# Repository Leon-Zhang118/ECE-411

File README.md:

# ECE Capstone Project 

# Teammates:

  Zheliang Zhang 

  Jinghan Zhang 

  Danny Wu

  Benjamin Vu

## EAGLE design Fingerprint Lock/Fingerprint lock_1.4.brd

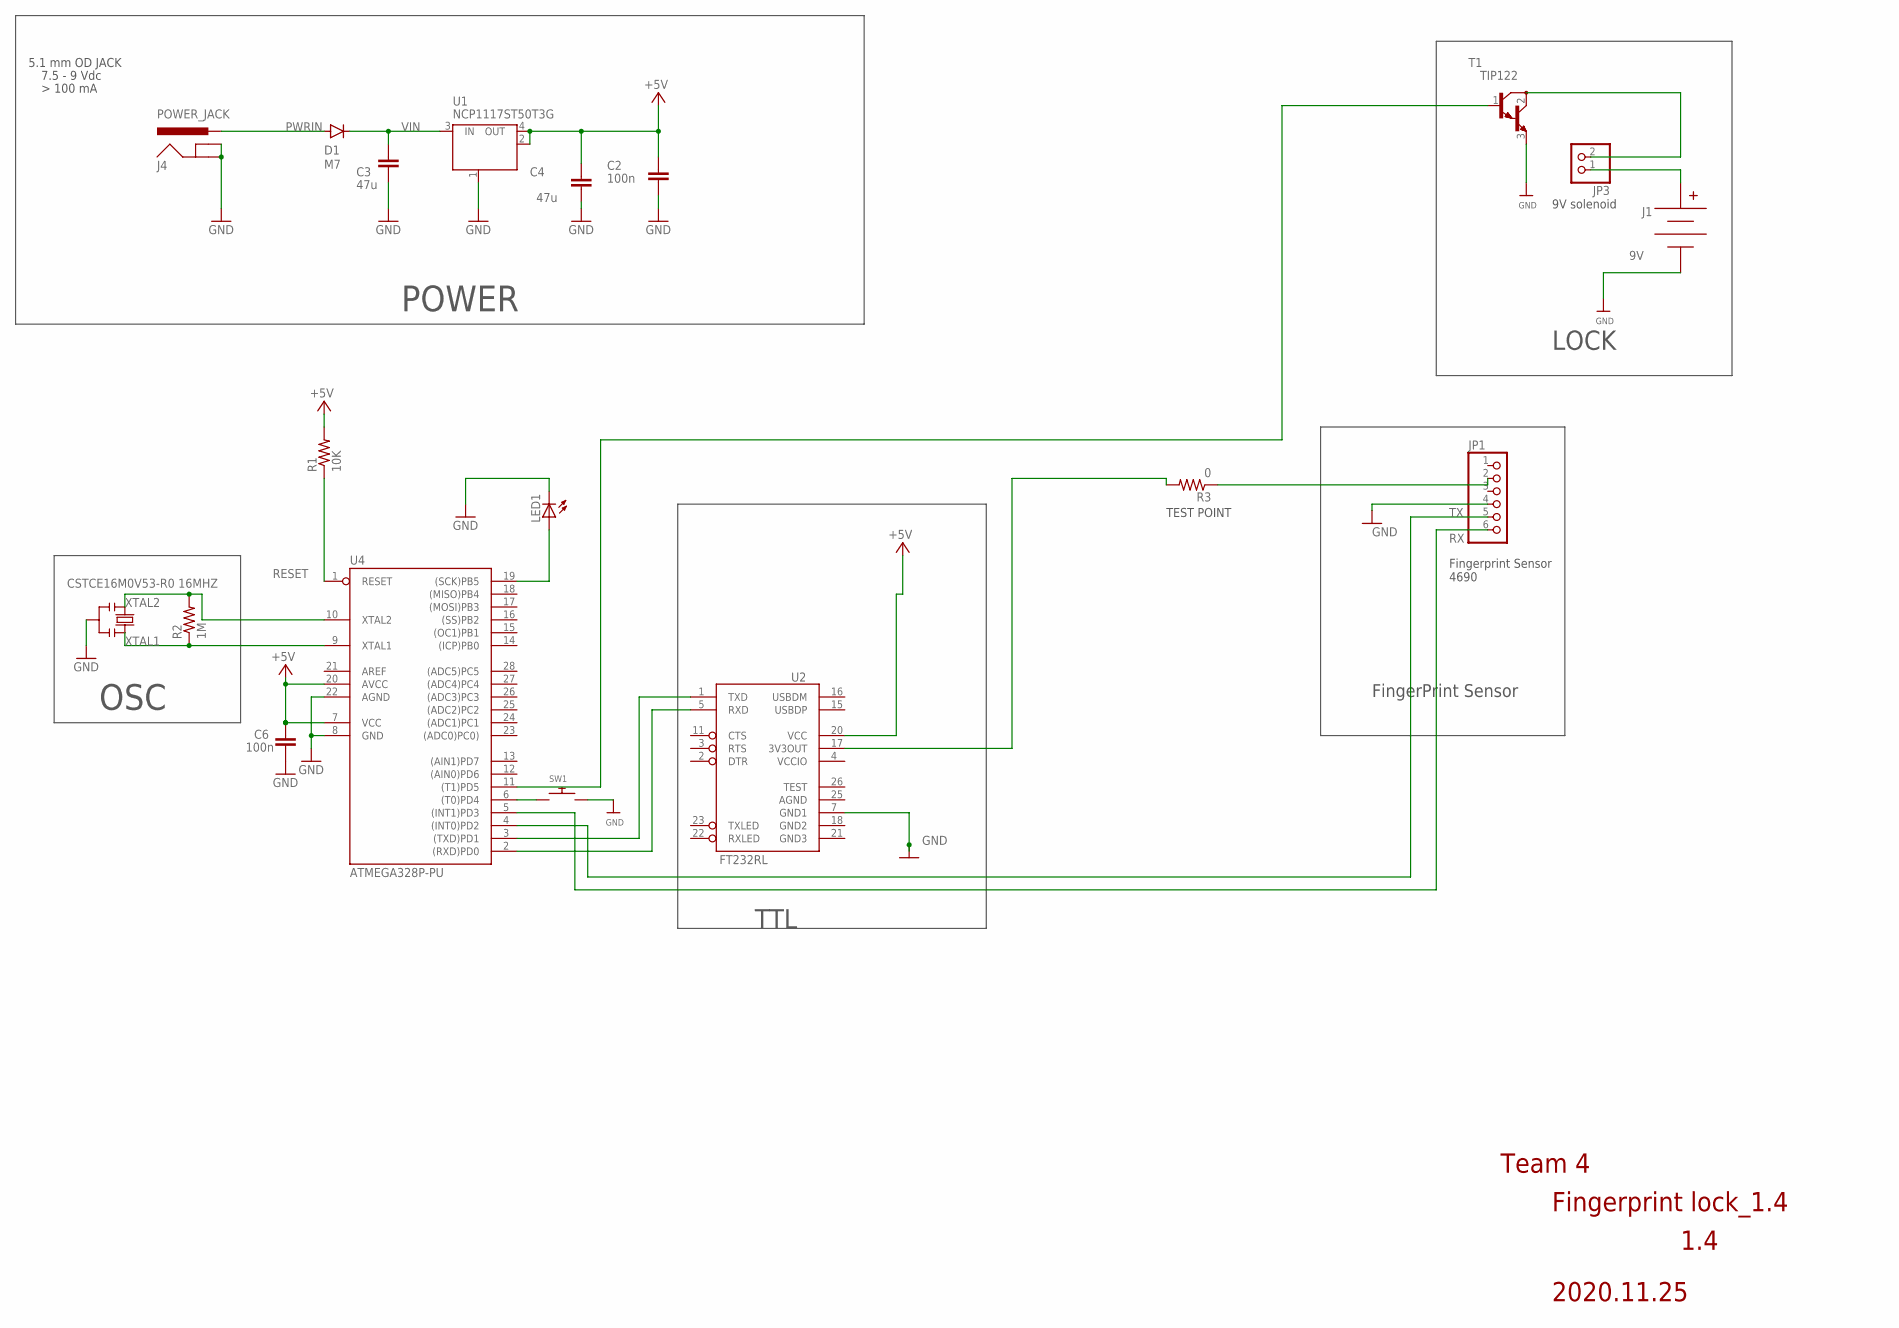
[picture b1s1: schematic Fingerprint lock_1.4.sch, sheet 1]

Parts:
C2, C6: 100n; C0805
C3, C4: 47u; C0805
D1: M7; SMB
J1: 9V; BC9VPC
J4: POWER_JACK; POWER_JACK_PTH
JP1: PINHD-1X6B; 1X06-BIG
JP3: PINHD-1X2; 1X02
LED1: LEDB155; Q62902-B155
R1: 10K; R0805
R2: 1M; R0805
R3: 0; R0805
SW1: SWITCH_PUSHBUTTONEVQ-PE; TACT_PANA-EVQ
T1: TIP122; TO220
U1: NCP1117ST50T3G; SOT223
U2: FT232RL; SSOP28DB
U4: ATMEGA328P-PU; DIL28-3
X1: CSTCE16M0V53-R0 16MHZ; RESONATOR

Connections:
9V: J1.V+, JP3.1
+5V: C2.2, C4.2, C6.2, R1.2, U1.2 (OUT), U1.4 (OUT), U2.20 (VCC), U4.7 (VCC), U4.20 (AVCC)
AGND: U2.25 (AGND)
GND: C2.1, C3.1, C4.1, C6.1, J1.V-, J4.GND, J4.GNDBREAK, JP1.4, LED1.K (C), SW1.P$2, T1.3 (E), U1.1 (GND/ADJ), U2.7 (GND1), U4.8 (GND), U4.22 (AGND), X1.2
GND2: U2.18 (GND2)
GND3: U2.21 (GND3)
LED: LED1.A, U4.19 ((SCK)PB5)
LOCK: T1.1 (B), U4.11 ((T1)PD5)
unnamed: JP1.6, U4.5 ((INT1)PD3)
unnamed: JP1.2, R3.1
unnamed: U2.5 (RXD), U4.2 ((RXD)PD0)
unnamed: U2.1 (TXD), U4.3 ((TXD)PD1)
unnamed: R3.2, U2.17 (3V3OUT)
unnamed: JP3.2, T1.2 (C)
unnamed: SW1.P$1, U4.6 ((T0)PD4)
PWRIN: D1.A, J4.PWR
RESET: R1.1, U4.1 (RESET)
TXD: JP1.5, U4.4 ((INT0)PD2)
VCCIO: U2.4 (VCCIO)
VIN: C3.2, D1.C, U1.3 (IN)
XTAL1: R2.1, U4.9 (XTAL1), X1.3
XTAL2: R2.2, U4.10 (XTAL2), X1.1

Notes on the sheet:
7.5 - 9 Vdc
POWER
OSC
5.1 mm OD JACK
Team 4
Fingerprint Sensor 4690
LOCK
FingerPrint Sensor
2020.11.25
TTL
9V solenoid
TEST POINT
Fingerprint lock_1.4
1.4

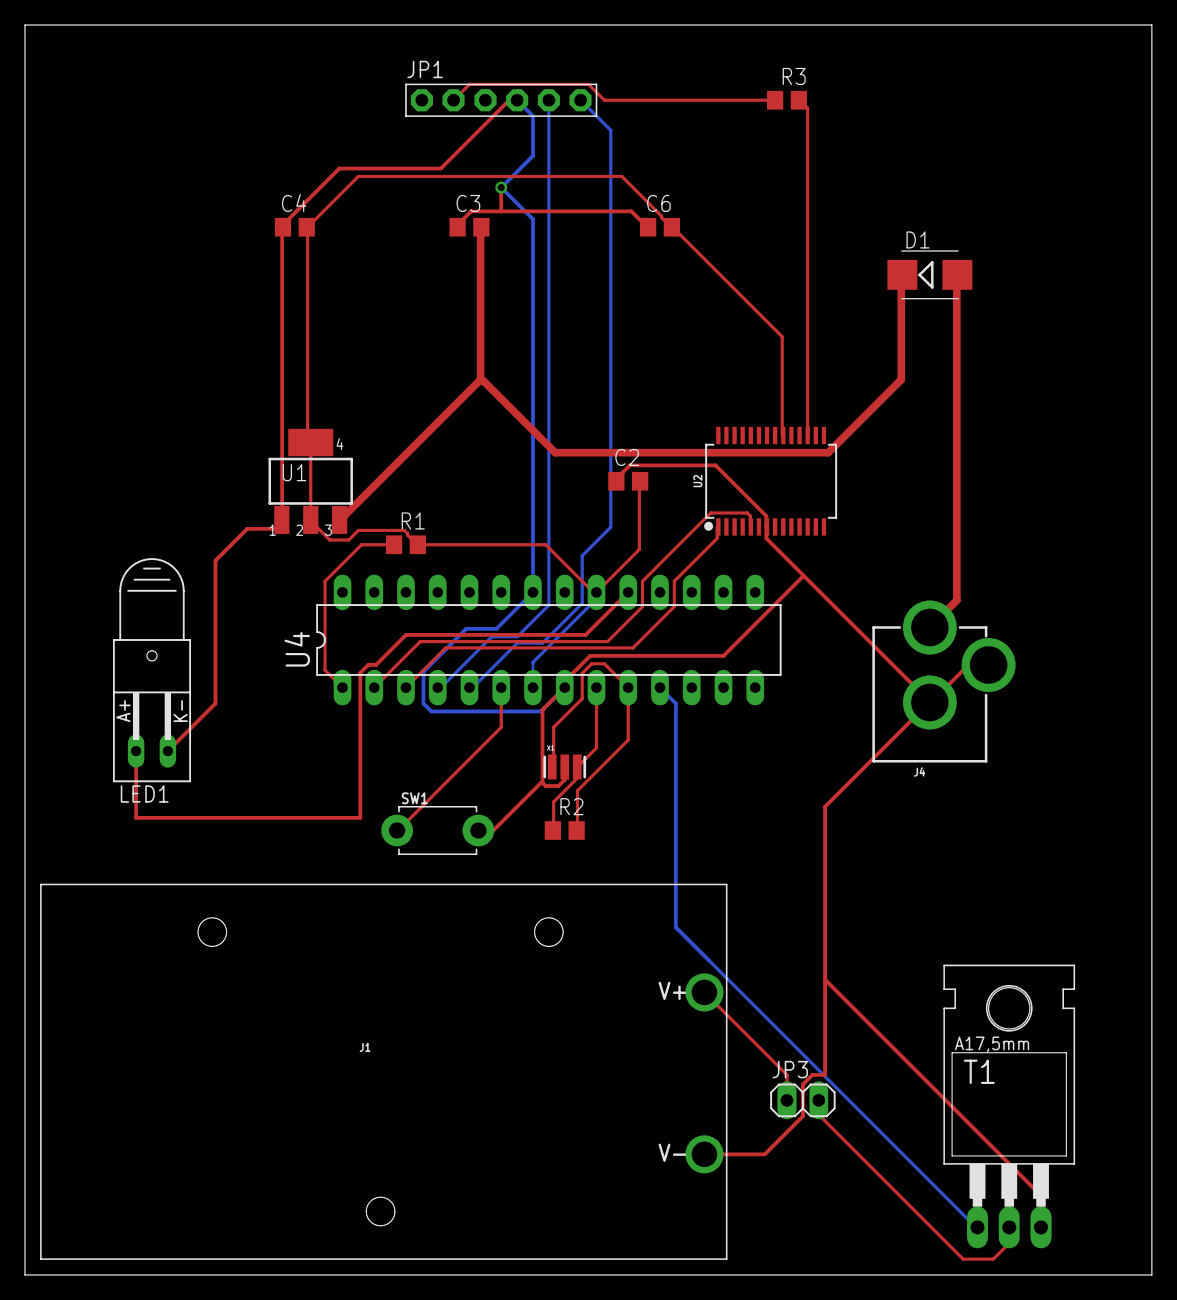
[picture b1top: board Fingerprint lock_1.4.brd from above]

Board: 4 copper layers, 90.2 x 100.0 mm, 19 parts (0 on the bottom side), 18 nets.

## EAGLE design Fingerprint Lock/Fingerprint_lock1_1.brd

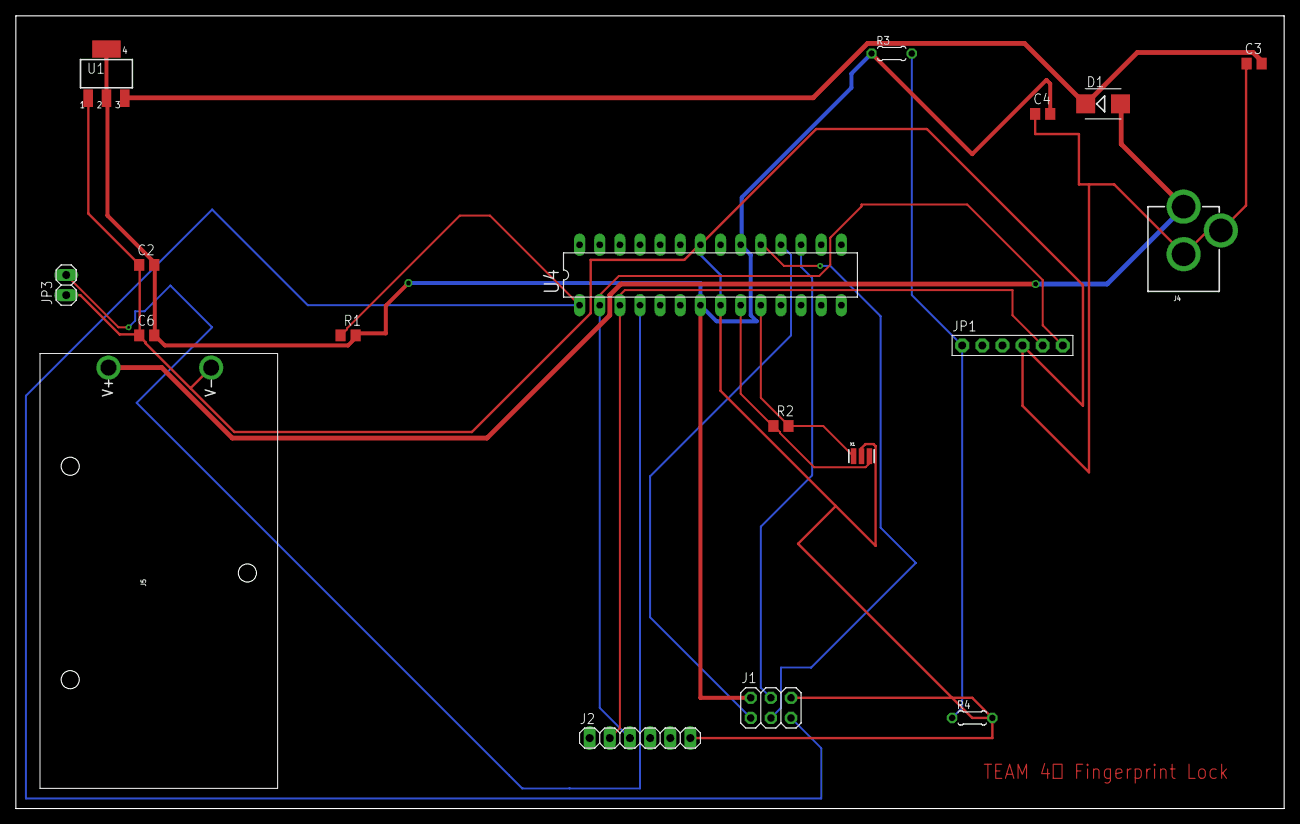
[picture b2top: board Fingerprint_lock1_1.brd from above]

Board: 2 copper layers, 160.0 x 100.0 mm, 18 parts (0 on the bottom side), 14 nets.

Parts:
C2, C6: 100n; C0805
C3, C4: 47u; C0805
D1: M7; SMB
J1: 3x2 M; 2X03
J2: 1X06
J4: POWER_JACK; POWER_JACK_PTH
J5: BC9VPC
JP1: 1X06-BIG
JP3: 1X02
R1: 10K; R0805
R2: 1M; R0805
R3: 5K; 0204/5
R4: 10K; 0204/5
U1: NCP1117ST50T3G; SOT223
U4: ATMEGA328P-PU; DIL28-3
X1: CSTCE16M0V53-R0 16MHZ; RESONATOR

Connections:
+5V: C2.2, C4.2, C6.2, J1.2, R1.2, R3.1, U1.2, U1.4, U4.7, U4.20
GND: C2.1, C3.1, C4.1, C6.1, J1.6, J2.6, J4.GND, J4.GNDBREAK, J5.V-, JP1.4, JP3.1, R4.2, U1.1, U4.8, U4.22, X1.2
MISO: J1.1, U4.18
MOSI: J1.4, U4.17
unnamed: JP1.1, R3.2, R4.1
PWRIN: D1.A, J4.PWR, J5.V+
RESET: J1.5, R1.1, U4.1
RXD: J2.3, JP1.6, U4.2
SCK: J1.3, U4.19
SLOCK: JP3.2, U4.4
TXD: J2.2, JP1.5, U4.3
VIN: C3.2, D1.C, U1.3
XTAL1: R2.1, U4.9, X1.3
XTAL2: R2.2, U4.10, X1.1

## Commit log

2020-10-04 Code
2020-10-15 Create WPRs
2020-10-15 Update WPRs
2020-10-20 Add files via upload
    PDS Revision 2
2020-11-01 Add files via upload
    Version 1.0
2020-11-02 Add files via upload
    bread prototype version 1.0
2020-11-02 Add files via upload
    1st Revision of fingerprint lock
2020-11-12 Add files via upload
    BOM
2020-11-12 Add files via upload
    Enter Fingerprint
2020-11-13 Add files via upload
    Project schedule
2020-11-19 Rename Fingerprint lock(Leon).ino to Fingerprint lock.ino
2020-11-19 Add files via upload
    Board Review
2020-11-26 Add files via upload
    Newest schematic and layout for fingerprint lock
2020-12-05 Add files via upload
    Final rev of schematic and layout

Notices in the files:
parts and their libraries:
SparkFun-Connectors: Licensing: Creative Commons ShareAlike 4.0 International - https://creativecommons.org/licenses/by-sa/4.0
